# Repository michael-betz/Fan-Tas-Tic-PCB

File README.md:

# Fan-Tas-Tic-PCB
Kicad files for the Fan-Tas-Tic pinball controller.
No tiny SMD components, can be easily assembled by hand.
Designed for the milling machine (2 sided but no real vias, using through hole components instead).

# Mainboard

[Schematic](https://raw.githubusercontent.com/yetifrisstlama/Fan-Tas-Tic-PCB/master/Mainboard/pdf/fan_tas_tic.pdf)

 * Based on TM4C123GXL evaluation board
 * 8 x 8 Switch matrix inputs (Operating on 12 V)
 * 12 x on-board open drain drivers for solenoids
 * 4 of them can do hardware PWM (> 100 kHz)
 * Fused in groups of 4
 * 4 x I2C channels for hardware extension boards.
   In- / Outputs can be easily and cheaply added with PCF8574 I2C GPIO extenders
 * 3 x SPI channels for running WS2811 / WS2812 LED strings.
   Up to 1024 LEDs / channel.
 * USB virtual serial connection to host PC (or Raspberry PI)
 * 5 V can come from USB or from external 24 V input (Set JP1)
 * SMD resistors / capacitors = 0805
 * Switch matrix driver:
   [TPIC6B595](http://www.ti.com/lit/ds/symlink/tpic6b595.pdf) (eBay)
 * GPIO extender:
   [PCF8574](http://www.ti.com/lit/ds/symlink/pcf8574.pdf) (eBay)
 * Dual power mosfet driver:
   [UCC27524](http://www.ti.com/lit/ds/symlink/ucc27524.pdf)
 * Power mosfets:
   [IRL640](http://www.vishay.com/docs/91305/91305.pdf)
 * Signal mosfet for I2C level conversion:
   [BSS138](https://www.fairchildsemi.com/datasheets/BS/BSS138.pdf)
 * 8 pin solenoid and 4 pin power connectors:
   [HT396](https://www.google.com/search?btnG=1&pws=0&q=Green+HT396+3.96mm+Straight+Pluggable+Screw+Terminal+Block+Connector&gws_rd=cr,ssl&ei=fLGbVpy5GMX4apzWrtgK)
 * 8 pin switch-matrix and 4 pin I2C connectors:
   [KF2510](https://www.google.com/search?btnG=1&pws=0&q=KF2510+2P-10P+2.54mm+Straight+/+Right-Angle+Connector+Header%2BTerminal%2BHousing&gws_rd=cr,ssl&ei=HrKbVpHDFoKua7iAu-AK)

## Status
The current version of the Mainboard PCB (06/2016) has been tested and worked as expected without any major problems. See also the [development blog](http://yetifrisstlama.blogspot.fr/). For the next revision, these (minor) issues will be fixed:
 * `Debug` USB connector on the Tiva board interferes with the I2C connectors on the mainboard. These will be moved.
 * An `Interlock` Relay will be introduced on the 24 V supply line for the solenoid drivers. This is needed as the I2C port extenders have by default all outputs active before beeing initialized (which only happens a few 10 ms after power up). Furthermore, if the firmware crashes, has I2C connection issues or locks up, it can cut the power from an fault-handler.
 * Freewheeling diodes _MUST_ be Schottky diodes and will be included on the PCB next to the mosfets (not on the solenoids!) for accetable EMI performance. This has been found experimentally (http://yetifrisstlama.blogspot.fr/).
 * More footprints for decoupling caps will be included

# Input extension board

[Schematic](https://raw.githubusercontent.com/yetifrisstlama/Fan-Tas-Tic-PCB/master/InputExtension/pdf/InputExtension.pdf)

 * 8 shiny new input channels for your pinball machine
 * as simple and cheap as it gets
 * read out a zooming 1000 times a second

## Status
[Built, tested, works as expected :)](https://yetifrisstlama.github.io/fan-tas-tic-score-reels/)

# Output extension board

[Schematic](https://raw.githubusercontent.com/yetifrisstlama/Fan-Tas-Tic-PCB/master/OutputExtension/pdf/OutputExtension.pdf)

 * 8 beefy open drain outputs to rock some solenoids
 * BYOM! Bring your own mosfets ... supports TO-220, TO-263 and SOT23 footprints
 * Fused, to keep the magic smoke in
 * Also drives motors, LED strings, LED floodlights ...

## Status
Built, tested, no issues found. Drives my score reels like a charm.

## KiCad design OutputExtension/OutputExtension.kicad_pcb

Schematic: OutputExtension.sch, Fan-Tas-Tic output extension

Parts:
C1, C2, C3, C4: 1u; C_0805_2012Metric
C5, C6: 470 uF; C_Radial_D10_L16_P5
D1, D2: LED; LED_0805_2012Metric
F1: FUSE; LBL_FUSE
F2: FUSE_DNP; littlefuse_154_smd
JP1: A0; PinHeader_1x03_P2.54mm_Vertical
JP2: A1; PinHeader_1x03_P2.54mm_Vertical
JP3: A2; PinHeader_1x03_P2.54mm_Vertical
P1, P2: CONN_01X04; PinHeader_1x04_P2.54mm_Vertical
P3: CONN_01X04; HT396_4
P4, P5: CONN_01X08; HT396_8
R1: 2200; R_0805_2012Metric
R2: 220; R_0805_2012Metric
U1: PCF8574; SOIC-16_7.5x10.3mm_Pitch1.27mm

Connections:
+5V: C1.1, C2.1, C4.1, JP1.3, JP2.3, JP3.3, P1.1, P2.1, R2.2, U1.16 (VCC)
+24V: C3.1, C5.1, C6.1, F1.2, F2.2, P4.1, P4.3, P4.5, P4.7, P5.1, P5.3, P5.5, P5.7, R1.2; also elsewhere on the board
/A0: JP1.2, U1.1 (A0)
/A1: JP2.2, U1.2 (A1)
/A2: JP3.2, U1.3 (A2)
/I2C_SCL: P1.2, P2.2, U1.14 (SCL)
/I2C_SDA: P1.3, P2.3, U1.15 (SDA)
/powerChannel0/CTRL: U1.4 (P0); also elsewhere on the board
/powerChannel0/DRAIN: P4.2; also elsewhere on the board
/powerChannel1/CTRL: U1.5 (P1); also elsewhere on the board
/powerChannel1/DRAIN: P4.4; also elsewhere on the board
/powerChannel2/CTRL: U1.6 (P2); also elsewhere on the board
/powerChannel2/DRAIN: P4.6; also elsewhere on the board
/powerChannel3/CTRL: U1.7 (P3); also elsewhere on the board
/powerChannel3/DRAIN: P4.8; also elsewhere on the board
/powerChannel4/CTRL: U1.9 (P4); also elsewhere on the board
/powerChannel4/DRAIN: P5.2; also elsewhere on the board
/powerChannel5/CTRL: U1.10 (P5); also elsewhere on the board
/powerChannel5/DRAIN: P5.4; also elsewhere on the board
/powerChannel6/CTRL: U1.11 (P6); also elsewhere on the board
/powerChannel6/DRAIN: P5.6; also elsewhere on the board
/powerChannel7/CTRL: U1.12 (P7); also elsewhere on the board
/powerChannel7/DRAIN: P5.8; also elsewhere on the board
unnamed: D1.2 (A), R1.1
unnamed: D2.2 (A), R2.1
unnamed: F1.1, F2.1, P3.3, P3.4

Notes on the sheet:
24 V power IN
Rev1: Change freeweeling diode footprint to SMC

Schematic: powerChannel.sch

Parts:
D3: SS310; D_SMC
Q1: IRL640; TO-220-3_Vertical
Q2: BSS138; SOT-23
Q3: 35N15; TO-263-3_TabPin2
R3: 470R; R_0805_2012Metric

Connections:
+24V: D3.1; also elsewhere on the board
/powerChannel0/CTRL: R3.2; also elsewhere on the board
/powerChannel0/DRAIN: D3.2, Q1.2 (D), Q2.3, Q3.2 (D); also elsewhere on the board
unnamed: Q1.1 (G), Q2.1, Q3.1 (G), R3.1

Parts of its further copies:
D4, D5, D6, D7, D8, D9, D10: SS310; D_SMC
Q4, Q7, Q10, Q13, Q16, Q19, Q22: IRL640; TO-220-3_Vertical
Q5, Q8, Q11, Q14, Q17, Q20, Q23: BSS138; SOT-23
Q6, Q9, Q12, Q15, Q18, Q21, Q24: 35N15; TO-263-3_TabPin2
R4, R5, R6, R7, R8, R9, R10: 470R; R_0805_2012Metric

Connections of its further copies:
+24V: D4.1, D5.1, D6.1, D7.1, D8.1, D9.1, D10.1; also elsewhere on the board
/powerChannel1/CTRL: R4.2; also elsewhere on the board
/powerChannel1/DRAIN: D4.2, Q4.2 (D), Q5.3, Q6.2 (D); also elsewhere on the board
/powerChannel2/CTRL: R5.2; also elsewhere on the board
/powerChannel2/DRAIN: D5.2, Q7.2 (D), Q8.3, Q9.2 (D); also elsewhere on the board
/powerChannel3/CTRL: R6.2; also elsewhere on the board
/powerChannel3/DRAIN: D6.2, Q10.2 (D), Q11.3, Q12.2 (D); also elsewhere on the board
/powerChannel4/CTRL: R7.2; also elsewhere on the board
/powerChannel4/DRAIN: D7.2, Q13.2 (D), Q14.3, Q15.2 (D); also elsewhere on the board
/powerChannel5/CTRL: R8.2; also elsewhere on the board
/powerChannel5/DRAIN: D8.2, Q16.2 (D), Q17.3, Q18.2 (D); also elsewhere on the board
/powerChannel6/CTRL: R9.2; also elsewhere on the board
/powerChannel6/DRAIN: D9.2, Q19.2 (D), Q20.3, Q21.2 (D); also elsewhere on the board
/powerChannel7/CTRL: R10.2; also elsewhere on the board
/powerChannel7/DRAIN: D10.2, Q22.2 (D), Q23.3, Q24.2 (D); also elsewhere on the board
unnamed: Q4.1 (G), Q5.1, Q6.1 (G), R4.1
unnamed: Q7.1 (G), Q8.1, Q9.1 (G), R5.1
unnamed: Q10.1 (G), Q11.1, Q12.1 (G), R6.1
unnamed: Q13.1 (G), Q14.1, Q15.1 (G), R7.1
unnamed: Q16.1 (G), Q17.1, Q18.1 (G), R8.1
unnamed: Q19.1 (G), Q20.1, Q21.1 (G), R9.1
unnamed: Q22.1 (G), Q23.1, Q24.1 (G), R10.1

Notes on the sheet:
DNP

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
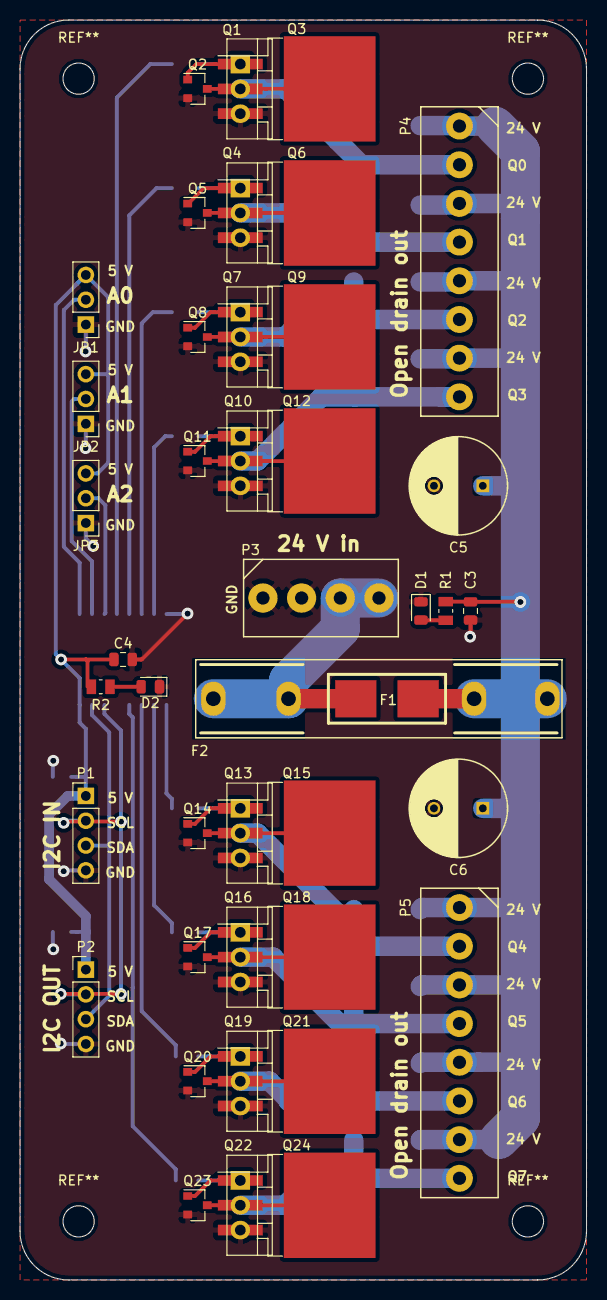
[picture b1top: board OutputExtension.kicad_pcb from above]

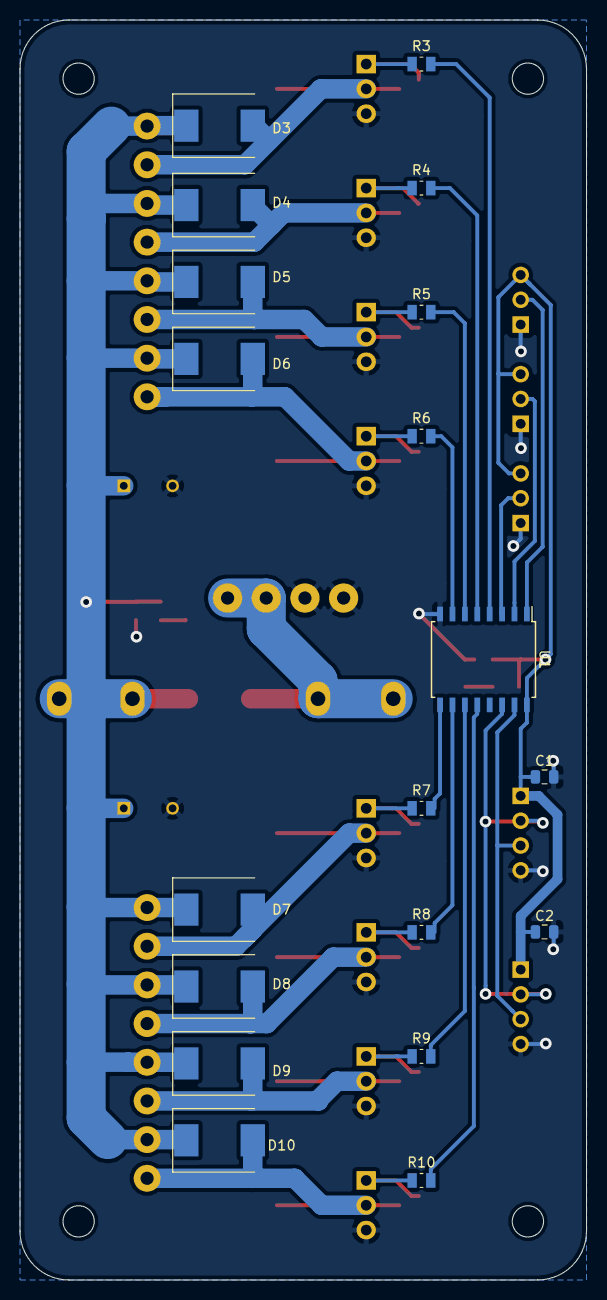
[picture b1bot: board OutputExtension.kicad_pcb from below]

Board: 2 copper layers, 58.0 x 129.0 mm, 61 parts (19 on the bottom side), 35 nets.

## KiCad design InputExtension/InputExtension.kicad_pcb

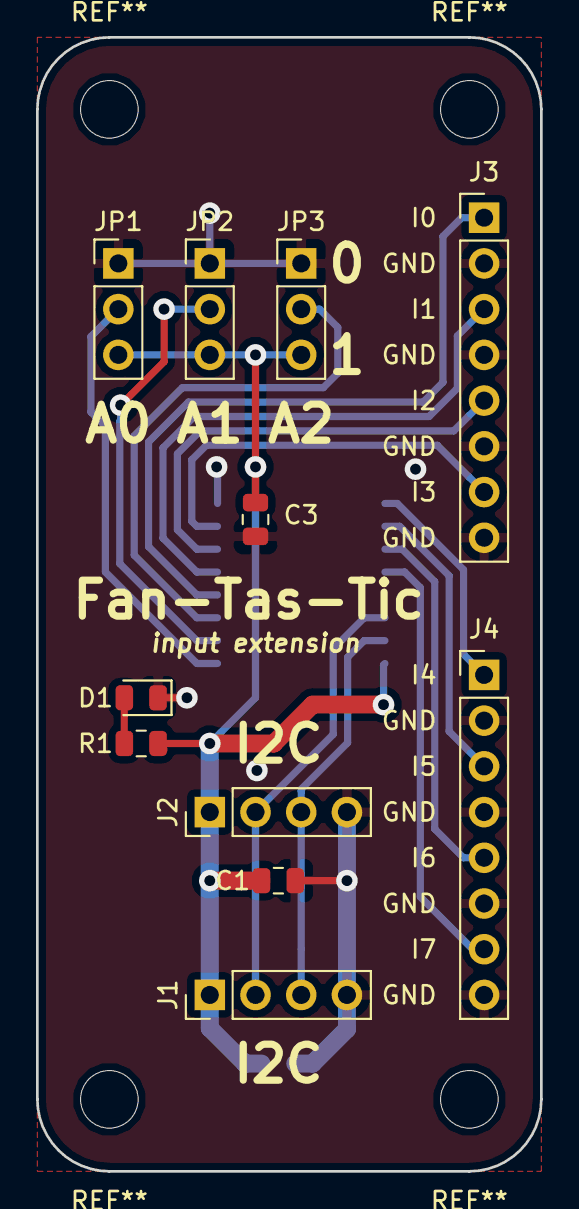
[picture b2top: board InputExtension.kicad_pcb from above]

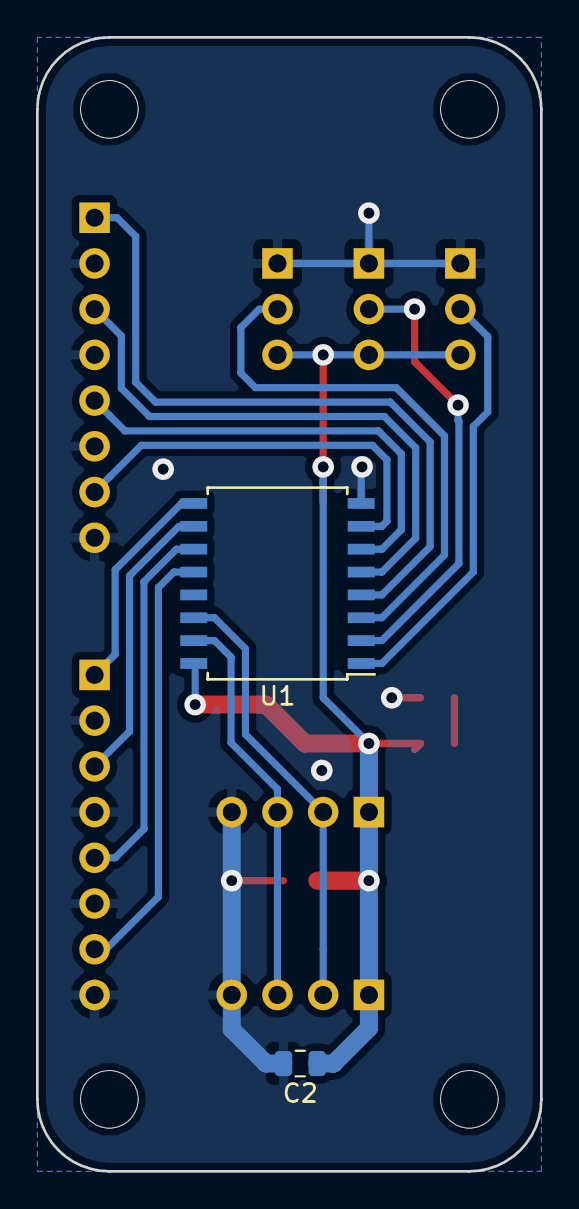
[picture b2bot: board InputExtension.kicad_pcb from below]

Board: 2 copper layers, 28.0 x 63.0 mm, 13 parts (2 on the bottom side), 16 nets.

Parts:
C1, C2, C3: 1u; C_0805_2012Metric
D1: LED; LED_0805_2012Metric
J1, J2: Conn_01x04; PinHeader_1x04_P2.54mm_Vertical
J3, J4: Conn_01x08; PinHeader_1x08_P2.54mm_Vertical
JP1, JP2, JP3: JP; PinHeader_1x03_P2.54mm_Vertical
R1: 220R; R_0805_2012Metric
U1: PCF8574; SOIC-16W_7.5x10.3mm_P1.27mm

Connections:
+5V: C1.1, C2.1, C3.1, J1.1, J2.1, JP1.3, JP2.3, JP3.3, R1.1, U1.16
/A0: JP1.2, U1.1
/A1: JP2.2, U1.2
/A2: JP3.2, U1.3
/I2C_SCL: J1.2, J2.2, U1.14
/I2C_SDA: J1.3, J2.3, U1.15
GND: C1.2, C2.2, C3.2, D1.1, J1.4, J2.4, J3.2, J3.4, J3.6, J3.8, J4.2, J4.4, J4.6, J4.8, JP1.1, JP2.1, JP3.1, U1.8
unnamed: D1.2, R1.2
unnamed: J3.1, U1.4
unnamed: J3.3, U1.5
unnamed: J3.5, U1.6
unnamed: J3.7, U1.7
unnamed: J4.1, U1.9
unnamed: J4.3, U1.10
unnamed: J4.5, U1.11
unnamed: J4.7, U1.12

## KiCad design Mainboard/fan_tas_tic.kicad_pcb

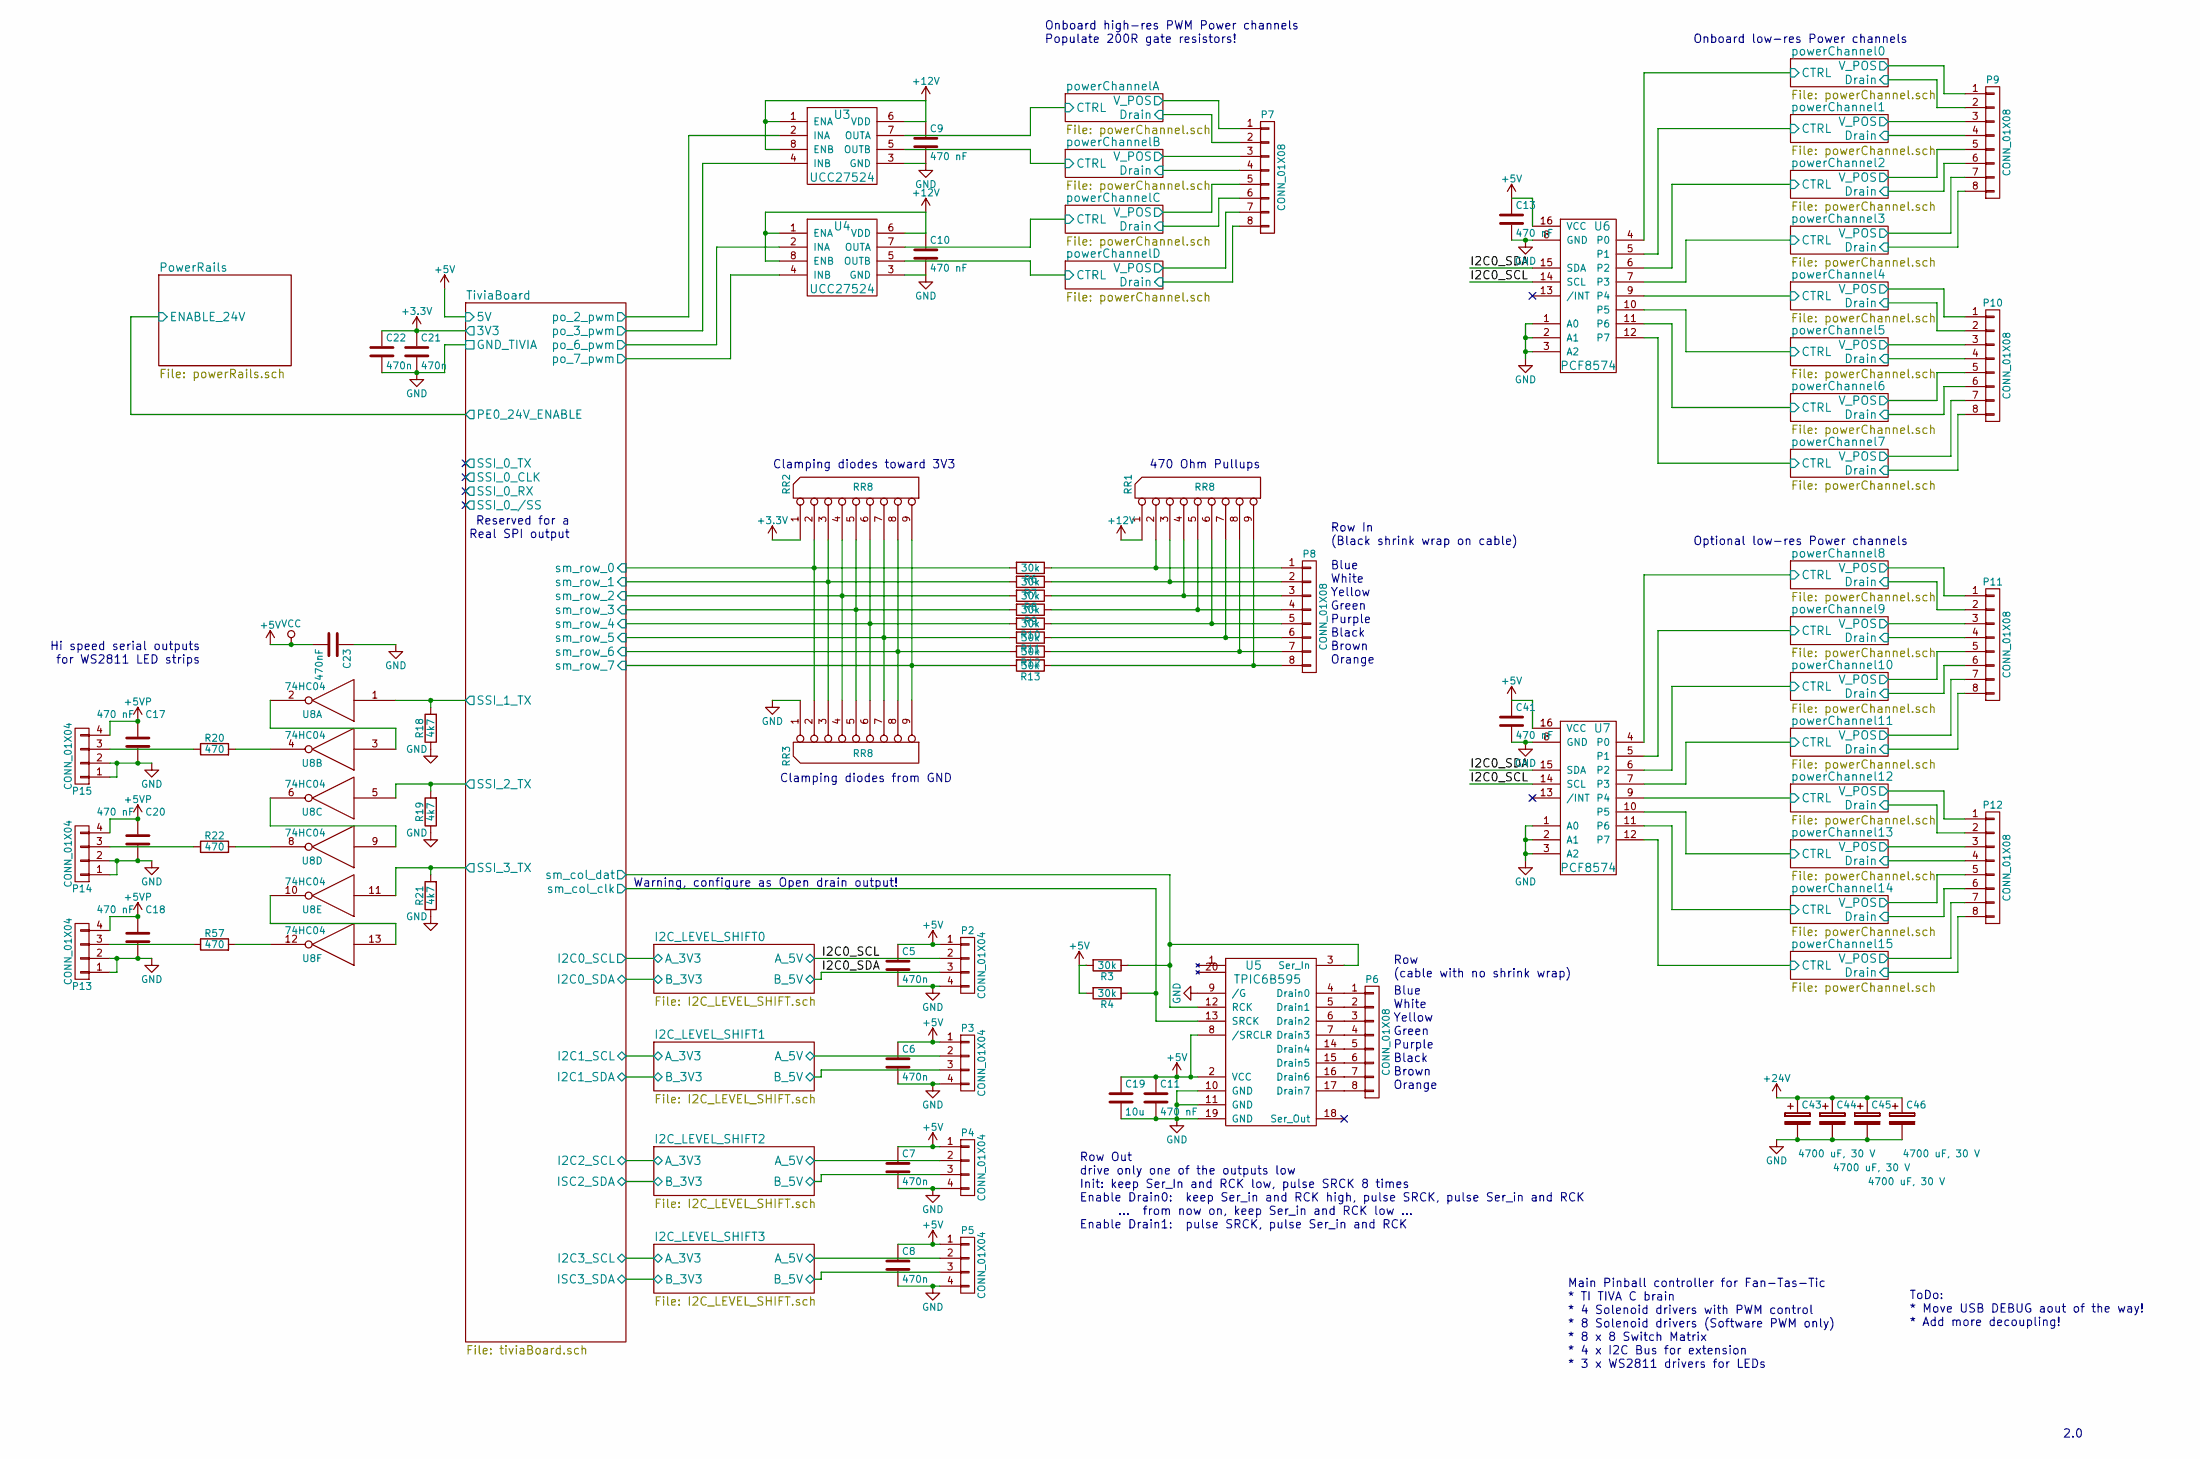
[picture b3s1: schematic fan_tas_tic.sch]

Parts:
C5, C6, C7, C8, C21, C22: 470n; C_0805_HandSoldering
C9, C10, C11, C13, C17, C18, C20, C41: 470 nF; C_0805_HandSoldering
C19: 10u; C_1210_HandSoldering
C23: 470nF; C_0805_HandSoldering
C43, C44: 4700 uF, 30 V; C_Radial_D18_L36_P7.5
C45, C46: 4700 uF, 30 V; C_Radial_D14_L25_P5
P2, P3, P4, P5: CONN_01X04; Pin_Header_Straight_1x04
P6, P8: CONN_01X08; Pin_Header_Straight_1x08
P7, P9, P10, P11, P12: CONN_01X08; HT396_8
P13, P14, P15: CONN_01X04; HT396_4
R3, R4, R6, R7, R8, R9, R10, R11, R12, R13: 30k; R_0805_HandSoldering
R18, R19, R21: 4k7; R_0805_HandSoldering
R20, R22, R57: 470; R_0805_HandSoldering
RR1, RR2, RR3: RR8; Resistor_Array_SIP8
U3, U4: UCC27524; DIP-8_W7.62mm_LongPads
U5: TPIC6B595; DIP-20_W7.62mm_LongPads
U6, U7: PCF8574; SOIC-16_7.5x10.3mm_Pitch1.27mm
U8: 74HC04; DIP-14_W7.62mm_LongPads

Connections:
+3V3: C21.1, C22.1, RR2.1 (COM); also elsewhere on the board
+5V: C5.1, C6.1, C7.1, C8.1, C11.1, C13.1, C19.1, C23.2, C41.1, P2.1, P3.1, P4.1, P5.1, R3.2, R4.2, U5.2 (VCC), U5.8 (/SRCLR), U6.16 (VCC), U7.16 (VCC), U8.14 (VCC); also elsewhere on the board
+5VP: C17.1, C18.1, C20.1, P13.4, P14.4, P15.4; also elsewhere on the board
+12V: C9.1, C10.1, RR1.1 (COM), U3.1 (ENA), U3.6 (VDD), U3.8 (ENB), U4.1 (ENA), U4.6 (VDD), U4.8 (ENB); also elsewhere on the board
+24V: C43.1, C44.1, C45.1, C46.1, P7.1, P7.3, P7.5, P7.7, P9.1, P9.3, P9.5, P9.7, P10.1, P10.3, P10.5, P10.7, P11.1, P11.3, P11.5, P11.7, P12.1, P12.3, P12.5, P12.7; also elsewhere on the board
/I2C_LEVEL_SHIFT0/A_5V: P2.2, U6.14 (SCL), U7.14 (SCL); also elsewhere on the board
/I2C_LEVEL_SHIFT0/B_5V: P2.3, U6.15 (SDA), U7.15 (SDA); also elsewhere on the board
/I2C_LEVEL_SHIFT1/A_5V: P3.2; also elsewhere on the board
/I2C_LEVEL_SHIFT1/B_5V: P3.3; also elsewhere on the board
/I2C_LEVEL_SHIFT2/A_5V: P4.2; also elsewhere on the board
/I2C_LEVEL_SHIFT2/B_5V: P4.3; also elsewhere on the board
/I2C_LEVEL_SHIFT3/A_5V: P5.2; also elsewhere on the board
/I2C_LEVEL_SHIFT3/B_5V: P5.3; also elsewhere on the board
/TiviaBoard/SSI_1_TX: R18.2, U8.1; also elsewhere on the board
/TiviaBoard/SSI_2_TX: R19.2, U8.5; also elsewhere on the board
/TiviaBoard/SSI_3_TX: R21.2, U8.11; also elsewhere on the board
/TiviaBoard/po_2_pwm: U3.2 (INA); also elsewhere on the board
/TiviaBoard/po_3_pwm: U3.4 (INB); also elsewhere on the board
/TiviaBoard/po_6_pwm: U4.2 (INA); also elsewhere on the board
/TiviaBoard/po_7_pwm: U4.4 (INB); also elsewhere on the board
/TiviaBoard/sm_col_clk: R4.1, U5.13 (SRCK); also elsewhere on the board
/TiviaBoard/sm_col_dat: R3.1, U5.3 (Ser_In), U5.12 (RCK); also elsewhere on the board
/TiviaBoard/sm_row_0: R6.2, RR2.2, RR3.2; also elsewhere on the board
/TiviaBoard/sm_row_1: R7.2, RR2.3, RR3.3; also elsewhere on the board
/TiviaBoard/sm_row_2: R8.2, RR2.4, RR3.4; also elsewhere on the board
/TiviaBoard/sm_row_3: R9.2, RR2.5, RR3.5; also elsewhere on the board
/TiviaBoard/sm_row_4: R10.2, RR2.6, RR3.6; also elsewhere on the board
/TiviaBoard/sm_row_5: R11.2, RR2.7, RR3.7; also elsewhere on the board
/TiviaBoard/sm_row_6: R12.2, RR2.8, RR3.8; also elsewhere on the board
/TiviaBoard/sm_row_7: R13.2, RR2.9, RR3.9; also elsewhere on the board
/powerChannel0/CTRL: U6.4 (P0); also elsewhere on the board
/powerChannel0/DRAIN: P9.2; also elsewhere on the board
/powerChannel1/CTRL: U6.5 (P1); also elsewhere on the board
/powerChannel1/DRAIN: P9.4; also elsewhere on the board
/powerChannel2/CTRL: U6.6 (P2); also elsewhere on the board
/powerChannel2/DRAIN: P9.6; also elsewhere on the board
/powerChannel3/CTRL: U6.7 (P3); also elsewhere on the board
/powerChannel3/DRAIN: P9.8; also elsewhere on the board
/powerChannel4/CTRL: U6.9 (P4); also elsewhere on the board
/powerChannel4/DRAIN: P10.2; also elsewhere on the board
/powerChannel5/CTRL: U6.10 (P5); also elsewhere on the board
/powerChannel5/DRAIN: P10.4; also elsewhere on the board
/powerChannel6/CTRL: U6.11 (P6); also elsewhere on the board
/powerChannel6/DRAIN: P10.6; also elsewhere on the board
/powerChannel7/CTRL: U6.12 (P7); also elsewhere on the board
/powerChannel7/DRAIN: P10.8; also elsewhere on the board
/powerChannel8/CTRL: U7.4 (P0); also elsewhere on the board
/powerChannel8/DRAIN: P11.2; also elsewhere on the board
/powerChannel9/CTRL: U7.5 (P1); also elsewhere on the board
/powerChannel9/DRAIN: P11.4; also elsewhere on the board
/powerChannel10/CTRL: U7.6 (P2); also elsewhere on the board
/powerChannel10/DRAIN: P11.6; also elsewhere on the board
/powerChannel11/CTRL: U7.7 (P3); also elsewhere on the board
/powerChannel11/DRAIN: P11.8; also elsewhere on the board
/powerChannel12/CTRL: U7.9 (P4); also elsewhere on the board
/powerChannel12/DRAIN: P12.2; also elsewhere on the board
/powerChannel13/CTRL: U7.10 (P5); also elsewhere on the board
/powerChannel13/DRAIN: P12.4; also elsewhere on the board
/powerChannel14/CTRL: U7.11 (P6); also elsewhere on the board
/powerChannel14/DRAIN: P12.6; also elsewhere on the board
/powerChannel15/CTRL: U7.12 (P7); also elsewhere on the board
/powerChannel15/DRAIN: P12.8; also elsewhere on the board
/powerChannelA/CTRL: U3.7 (OUTA); also elsewhere on the board
/powerChannelA/DRAIN: P7.2; also elsewhere on the board
/powerChannelB/CTRL: U3.5 (OUTB); also elsewhere on the board
/powerChannelB/DRAIN: P7.4; also elsewhere on the board
/powerChannelC/CTRL: U4.7 (OUTA); also elsewhere on the board
/powerChannelC/DRAIN: P7.6; also elsewhere on the board
/powerChannelD/CTRL: U4.5 (OUTB); also elsewhere on the board
/powerChannelD/DRAIN: P7.8; also elsewhere on the board
GND: C5.2, C6.2, C7.2, C8.2, C9.2, C10.2, C11.2, C13.2, C17.2, C18.2, C19.2, C20.2, C21.2, C22.2, C23.1, C41.2, C43.2, C44.2, C45.2, C46.2, P2.4, P3.4, P4.4, P5.4, P13.1, P13.2, P14.1, P14.2, P15.1, P15.2, R18.1, R19.1, R21.1, RR3.1 (COM), U3.3 (GND), U4.3 (GND), U5.9 (/G), U5.10 (GND), U5.11 (GND), U5.19 (GND), U6.1 (A0), U6.2 (A1), U6.3 (A2), U6.8 (GND), U7.1 (A0), U7.2 (A1), U7.3 (A2), U7.8 (GND), U8.7 (GND); also elsewhere on the board
unnamed: P6.1, U5.4 (Drain0)
unnamed: P6.2, U5.5 (Drain1)
unnamed: P6.3, U5.6 (Drain2)
unnamed: P6.4, U5.7 (Drain3)
unnamed: P6.5, U5.14 (Drain4)
unnamed: P6.6, U5.15 (Drain5)
unnamed: P6.7, U5.16 (Drain6)
unnamed: P6.8, U5.17 (Drain7)
unnamed: P8.1, R6.1, RR1.2
unnamed: P8.2, R7.1, RR1.3
unnamed: P8.3, R8.1, RR1.4
unnamed: P8.4, R9.1, RR1.5
unnamed: P8.5, R10.1, RR1.6
unnamed: P8.6, R11.1, RR1.7
unnamed: P8.7, R12.1, RR1.8
unnamed: P8.8, R13.1, RR1.9
unnamed: P13.3, R57.1
unnamed: P14.3, R22.1
unnamed: P15.3, R20.1
unnamed: R20.2, U8.4
unnamed: R22.2, U8.8
unnamed: R57.2, U8.12
unnamed: U8.2, U8.3
unnamed: U8.6, U8.9
unnamed: U8.10, U8.13

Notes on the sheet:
Row Out drive only one of the outputs low Init: keep Ser_In and RCK low, pulse SRCK 8 times Enable Drain0: keep Ser_in and RCK high, pulse SRCK, pulse Ser_in and RCK ... from now on, keep Ser_in and RCK low ... Enable Drain1: pulse SRCK, pulse Ser_in and RCK
Row In (Black shrink wrap on cable)
Onboard high-res PWM Power channels Populate 200R gate resistors!
Onboard low-res Power channels
Warning, configure as Open drain output!
Main Pinball controller for Fan-Tas-Tic * TI TIVA C brain * 4 Solenoid drivers with PWM control * 8 Solenoid drivers (Software PWM only) * 8 x 8 Switch Matrix * 4 x I2C Bus for extension * 3 x WS2811 drivers for LEDs
Hi speed serial outputs for WS2811 LED strips
470 Ohm Pullups
Clamping diodes toward 3V3
Clamping diodes from GND
Reserved for a Real SPI output
ToDo: * Move USB DEBUG aout of the way! * Add more decoupling!
Blue White Yellow Green Purple Black Brown Orange
Row (cable with no shrink wrap)
2.0
Optional low-res Power channels

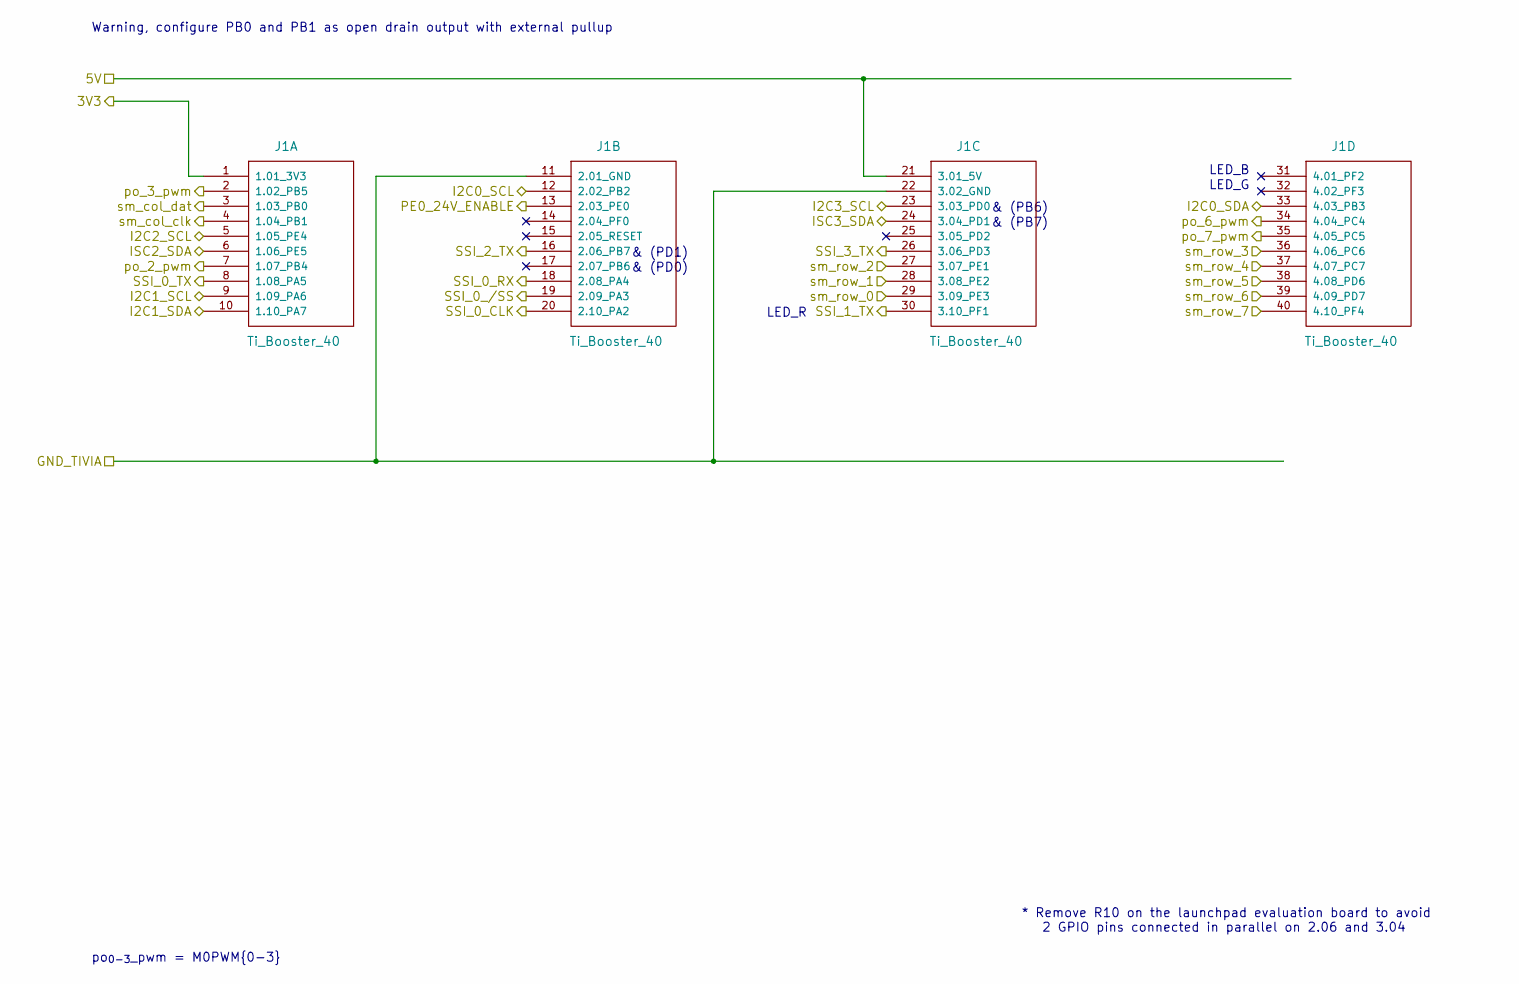
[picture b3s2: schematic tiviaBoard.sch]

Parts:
J1: Ti_Booster_40; Tivia_Launch_Pad

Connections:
+3V3: J1.1 (1.01_3V3); also elsewhere on the board
+5V: J1.21 (3.01_5V); also elsewhere on the board
/I2C_LEVEL_SHIFT0/A_3V3: J1.12 (2.02_PB2); also elsewhere on the board
/I2C_LEVEL_SHIFT0/B_3V3: J1.33 (4.03_PB3); also elsewhere on the board
/I2C_LEVEL_SHIFT1/A_3V3: J1.9 (1.09_PA6); also elsewhere on the board
/I2C_LEVEL_SHIFT1/B_3V3: J1.10 (1.10_PA7); also elsewhere on the board
/I2C_LEVEL_SHIFT2/A_3V3: J1.5 (1.05_PE4); also elsewhere on the board
/I2C_LEVEL_SHIFT2/B_3V3: J1.6 (1.06_PE5); also elsewhere on the board
/I2C_LEVEL_SHIFT3/A_3V3: J1.23 (3.03_PD0); also elsewhere on the board
/I2C_LEVEL_SHIFT3/B_3V3: J1.24 (3.04_PD1); also elsewhere on the board
/PowerRails/ENABLE_24V: J1.13 (2.03_PE0); also elsewhere on the board
/TiviaBoard/SSI_0_/SS: J1.19 (2.09_PA3)
/TiviaBoard/SSI_0_CLK: J1.20 (2.10_PA2)
/TiviaBoard/SSI_0_RX: J1.18 (2.08_PA4)
/TiviaBoard/SSI_0_TX: J1.8 (1.08_PA5)
/TiviaBoard/SSI_1_TX: J1.30 (3.10_PF1); also elsewhere on the board
/TiviaBoard/SSI_2_TX: J1.16 (2.06_PB7); also elsewhere on the board
/TiviaBoard/SSI_3_TX: J1.26 (3.06_PD3); also elsewhere on the board
/TiviaBoard/po_2_pwm: J1.7 (1.07_PB4); also elsewhere on the board
/TiviaBoard/po_3_pwm: J1.2 (1.02_PB5); also elsewhere on the board
/TiviaBoard/po_6_pwm: J1.34 (4.04_PC4); also elsewhere on the board
/TiviaBoard/po_7_pwm: J1.35 (4.05_PC5); also elsewhere on the board
/TiviaBoard/sm_col_clk: J1.4 (1.04_PB1); also elsewhere on the board
/TiviaBoard/sm_col_dat: J1.3 (1.03_PB0); also elsewhere on the board
/TiviaBoard/sm_row_0: J1.29 (3.09_PE3); also elsewhere on the board
/TiviaBoard/sm_row_1: J1.28 (3.08_PE2); also elsewhere on the board
/TiviaBoard/sm_row_2: J1.27 (3.07_PE1); also elsewhere on the board
/TiviaBoard/sm_row_3: J1.36 (4.06_PC6); also elsewhere on the board
/TiviaBoard/sm_row_4: J1.37 (4.07_PC7); also elsewhere on the board
/TiviaBoard/sm_row_5: J1.38 (4.08_PD6); also elsewhere on the board
/TiviaBoard/sm_row_6: J1.39 (4.09_PD7); also elsewhere on the board
/TiviaBoard/sm_row_7: J1.40 (4.10_PF4); also elsewhere on the board
GND: J1.11 (2.01_GND), J1.22 (3.02_GND); also elsewhere on the board

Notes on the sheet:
po_{0-3}_pwm = M0PWM{0-3}
Warning, configure PB0 and PB1 as open drain output with external pullup
LED_R
LED_B
LED_G
& (PD1)
& (PD0)
& (PB6)
& (PB7)
* Remove R10 on the launchpad evaluation board to avoid 2 GPIO pins connected in parallel on 2.06 and 3.04

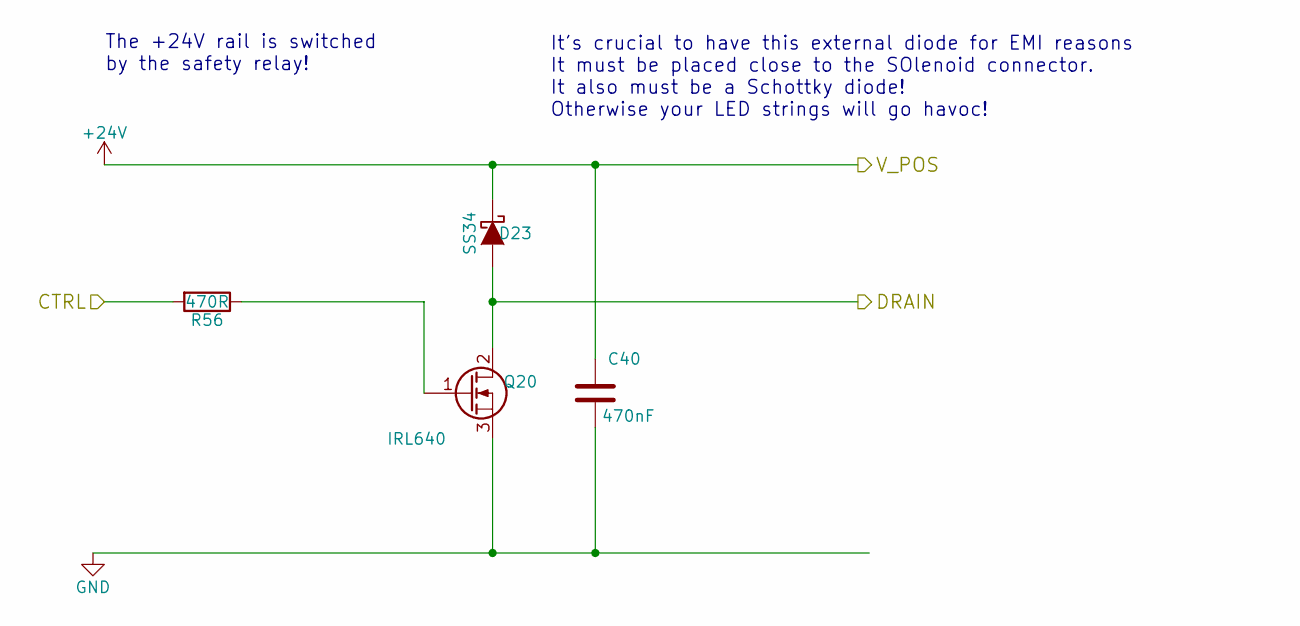
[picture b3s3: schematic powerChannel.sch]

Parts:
C25: 470nF; C_0805_HandSoldering
D8: SS34; SMC-RM10_Universal_Handsoldering
Q5: IRL640; TO-220_Neutral123_Vertical_LargePads
R23: 470R; R_0805_HandSoldering

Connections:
+24V: C25.1, D8.1 (K); also elsewhere on the board
/powerChannel0/CTRL: R23.2; also elsewhere on the board
/powerChannel0/DRAIN: D8.2 (A), Q5.2 (D); also elsewhere on the board
GND: C25.2, Q5.3 (S); also elsewhere on the board
unnamed: Q5.1 (G), R23.1

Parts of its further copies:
C12, C14, C15, C26, C27, C28, C29, C30, C31, C32, C33, C34, C35, C36, C37, C38, C39, C40, C42: 470nF; C_0805_HandSoldering
D4, D5, D6, D7, D9, D10, D11, D12, D13, D14, D15, D16, D17, D18, D19, D20, D21, D22, D23: SS34; SMC-RM10_Universal_Handsoldering
Q1, Q2, Q3, Q4, Q6, Q7, Q8, Q9, Q10, Q11, Q12, Q13, Q14, Q15, Q16, Q17, Q18, Q19, Q20: IRL640; TO-220_Neutral123_Vertical_LargePads
R1, R2, R5, R14, R24, R25, R26, R27, R28, R29, R30, R49, R50, R51, R52, R53, R54, R55, R56: 470R; R_0805_HandSoldering

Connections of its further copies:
+24V: C12.1, C14.1, C15.1, C26.1, C27.1, C28.1, C29.1, C30.1, C31.1, C32.1, C33.1, C34.1, C35.1, C36.1, C37.1, C38.1, C39.1, C40.1, C42.1, D4.1 (K), D5.1 (K), D6.1 (K), D7.1 (K), D9.1 (K), D10.1 (K), D11.1 (K), D12.1 (K), D13.1 (K), D14.1 (K), D15.1 (K), D16.1 (K), D17.1 (K), D18.1 (K), D19.1 (K), D20.1 (K), D21.1 (K), D22.1 (K), D23.1 (K); also elsewhere on the board
/powerChannel1/CTRL: R24.2; also elsewhere on the board
/powerChannel1/DRAIN: D9.2 (A), Q6.2 (D); also elsewhere on the board
/powerChannel2/CTRL: R25.2; also elsewhere on the board
/powerChannel2/DRAIN: D10.2 (A), Q7.2 (D); also elsewhere on the board
/powerChannel3/CTRL: R26.2; also elsewhere on the board
/powerChannel3/DRAIN: D11.2 (A), Q8.2 (D); also elsewhere on the board
/powerChannel4/CTRL: R27.2; also elsewhere on the board
/powerChannel4/DRAIN: D12.2 (A), Q9.2 (D); also elsewhere on the board
/powerChannel5/CTRL: R28.2; also elsewhere on the board
/powerChannel5/DRAIN: D13.2 (A), Q10.2 (D); also elsewhere on the board
/powerChannel6/CTRL: R29.2; also elsewhere on the board
/powerChannel6/DRAIN: D14.2 (A), Q11.2 (D); also elsewhere on the board
/powerChannel7/CTRL: R30.2; also elsewhere on the board
/powerChannel7/DRAIN: D15.2 (A), Q12.2 (D); also elsewhere on the board
/powerChannel8/CTRL: R49.2; also elsewhere on the board
/powerChannel8/DRAIN: D16.2 (A), Q13.2 (D); also elsewhere on the board
/powerChannel9/CTRL: R50.2; also elsewhere on the board
/powerChannel9/DRAIN: D17.2 (A), Q14.2 (D); also elsewhere on the board
/powerChannel10/CTRL: R51.2; also elsewhere on the board
/powerChannel10/DRAIN: D18.2 (A), Q15.2 (D); also elsewhere on the board
/powerChannel11/CTRL: R52.2; also elsewhere on the board
/powerChannel11/DRAIN: D19.2 (A), Q16.2 (D); also elsewhere on the board
/powerChannel12/CTRL: R53.2; also elsewhere on the board
/powerChannel12/DRAIN: D20.2 (A), Q17.2 (D); also elsewhere on the board
/powerChannel13/CTRL: R54.2; also elsewhere on the board
/powerChannel13/DRAIN: D21.2 (A), Q18.2 (D); also elsewhere on the board
/powerChannel14/CTRL: R55.2; also elsewhere on the board
/powerChannel14/DRAIN: D22.2 (A), Q19.2 (D); also elsewhere on the board
/powerChannel15/CTRL: R56.2; also elsewhere on the board
/powerChannel15/DRAIN: D23.2 (A), Q20.2 (D); also elsewhere on the board
/powerChannelA/CTRL: R1.2; also elsewhere on the board
/powerChannelA/DRAIN: D4.2 (A), Q1.2 (D); also elsewhere on the board
/powerChannelB/CTRL: R2.2; also elsewhere on the board
/powerChannelB/DRAIN: D5.2 (A), Q2.2 (D); also elsewhere on the board
/powerChannelC/CTRL: R5.2; also elsewhere on the board
/powerChannelC/DRAIN: D6.2 (A), Q3.2 (D); also elsewhere on the board
/powerChannelD/CTRL: R14.2; also elsewhere on the board
/powerChannelD/DRAIN: D7.2 (A), Q4.2 (D); also elsewhere on the board
GND: C12.2, C14.2, C15.2, C26.2, C27.2, C28.2, C29.2, C30.2, C31.2, C32.2, C33.2, C34.2, C35.2, C36.2, C37.2, C38.2, C39.2, C40.2, C42.2, Q1.3 (S), Q2.3 (S), Q3.3 (S), Q4.3 (S), Q6.3 (S), Q7.3 (S), Q8.3 (S), Q9.3 (S), Q10.3 (S), Q11.3 (S), Q12.3 (S), Q13.3 (S), Q14.3 (S), Q15.3 (S), Q16.3 (S), Q17.3 (S), Q18.3 (S), Q19.3 (S), Q20.3 (S); also elsewhere on the board
unnamed: Q1.1 (G), R1.1
unnamed: Q2.1 (G), R2.1
unnamed: Q3.1 (G), R5.1
unnamed: Q4.1 (G), R14.1
unnamed: Q6.1 (G), R24.1
unnamed: Q7.1 (G), R25.1
unnamed: Q8.1 (G), R26.1
unnamed: Q9.1 (G), R27.1
unnamed: Q10.1 (G), R28.1
unnamed: Q11.1 (G), R29.1
unnamed: Q12.1 (G), R30.1
unnamed: Q13.1 (G), R49.1
unnamed: Q14.1 (G), R50.1
unnamed: Q15.1 (G), R51.1
unnamed: Q16.1 (G), R52.1
unnamed: Q17.1 (G), R53.1
unnamed: Q18.1 (G), R54.1
unnamed: Q19.1 (G), R55.1
unnamed: Q20.1 (G), R56.1

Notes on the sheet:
It's crucial to have this external diode for EMI reasons It must be placed close to the SOlenoid connector. It also must be a Schottky diode! Otherwise your LED strings will go havoc!
The +24V rail is switched by the safety relay!

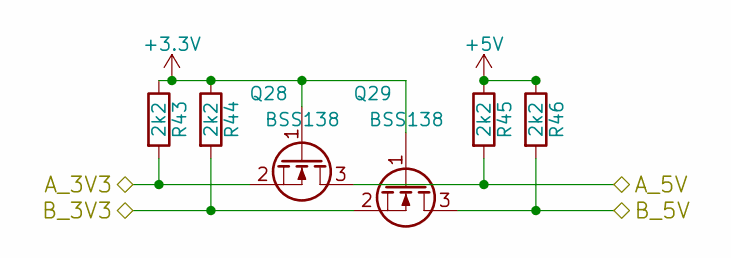
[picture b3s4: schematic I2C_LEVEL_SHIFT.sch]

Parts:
Q22, Q23: BSS138; SOT-23_Handsoldering
R31, R32, R33, R34: 2k2; R_0805_HandSoldering

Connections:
+3V3: Q22.1 (G), Q23.1 (G), R31.1, R32.1; also elsewhere on the board
+5V: R33.1, R34.1; also elsewhere on the board
/I2C_LEVEL_SHIFT0/A_3V3: Q22.2 (S), R31.2; also elsewhere on the board
/I2C_LEVEL_SHIFT0/A_5V: Q22.3 (D), R33.2; also elsewhere on the board
/I2C_LEVEL_SHIFT0/B_3V3: Q23.2 (S), R32.2; also elsewhere on the board
/I2C_LEVEL_SHIFT0/B_5V: Q23.3 (D), R34.2; also elsewhere on the board

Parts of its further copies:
Q24, Q25, Q26, Q27, Q28, Q29: BSS138; SOT-23_Handsoldering
R35, R36, R37, R38, R39, R40, R41, R42, R43, R44, R45, R46: 2k2; R_0805_HandSoldering

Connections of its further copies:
+3V3: Q24.1 (G), Q25.1 (G), Q26.1 (G), Q27.1 (G), Q28.1 (G), Q29.1 (G), R35.1, R36.1, R39.1, R40.1, R43.1, R44.1; also elsewhere on the board
+5V: R37.1, R38.1, R41.1, R42.1, R45.1, R46.1; also elsewhere on the board
/I2C_LEVEL_SHIFT1/A_3V3: Q24.2 (S), R35.2; also elsewhere on the board
/I2C_LEVEL_SHIFT1/A_5V: Q24.3 (D), R37.2; also elsewhere on the board
/I2C_LEVEL_SHIFT1/B_3V3: Q25.2 (S), R36.2; also elsewhere on the board
/I2C_LEVEL_SHIFT1/B_5V: Q25.3 (D), R38.2; also elsewhere on the board
/I2C_LEVEL_SHIFT2/A_3V3: Q26.2 (S), R39.2; also elsewhere on the board
/I2C_LEVEL_SHIFT2/A_5V: Q26.3 (D), R41.2; also elsewhere on the board
/I2C_LEVEL_SHIFT2/B_3V3: Q27.2 (S), R40.2; also elsewhere on the board
/I2C_LEVEL_SHIFT2/B_5V: Q27.3 (D), R42.2; also elsewhere on the board
/I2C_LEVEL_SHIFT3/A_3V3: Q28.2 (S), R43.2; also elsewhere on the board
/I2C_LEVEL_SHIFT3/A_5V: Q28.3 (D), R45.2; also elsewhere on the board
/I2C_LEVEL_SHIFT3/B_3V3: Q29.2 (S), R44.2; also elsewhere on the board
/I2C_LEVEL_SHIFT3/B_5V: Q29.3 (D), R46.2; also elsewhere on the board
